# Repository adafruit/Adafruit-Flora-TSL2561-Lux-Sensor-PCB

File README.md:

## Adafruit Flora TSL2561 Lux Sensor PCB

<a href="http://www.adafruit.com/products/1246"><br/>
Click here to purchase one from the Adafruit shop</a>

PCB files for the Adafruit Flora TSL2561 Lux Sensor. Format is EagleCAD schematic and board layout
* https://www.adafruit.com/product/1246

### DESCRIPTION
Add light-reactive sensing to your wearable Flora project with this high precision Lux sensor. The TSL2561 luminosity sensor is an advanced digital light sensor, ideal for use in a wide range of light situations. Compared to low cost CdS cells, this sensor is more precise, allowing for exact lux calculations and can be configured for different gain/timing ranges to detect light ranges from up to 0.1 - 40,000+ Lux on the fly. The best part of this sensor is that it contains both infrared and full spectrum diodes! That means you can separately measure infrared, full-spectrum or human-visible light. Most sensors can only detect one or the other, which does not accurately represent what human eyes see (since we cannot perceive the IR light that is detected by most photo diodes)

The sensor has a digital (I2C) interface. Attaching it to the flora is simple: line up the sensor so its adjacent to the SDA/SCL pins and sew conductive thread from the 3V, SDA, SCL and GND pins. They line up perfectly so you will not have any crossed lines. You can only connect one lux sensor to your Flora, but you can connect other I2C sensors/outputs by using the set of SCL/SDA pins on the opposite side. The current draw is extremely low, about 0.5mA when actively sensing, and less than 15 uA when in powerdown mode.

### License

Adafruit invests time and resources providing this open source design, please support Adafruit and open-source hardware by purchasing products from [Adafruit.com](https://www.adafruit.com)!

Designed by Adafruit Industries. 

Creative Commons Attribution, Share-Alike license, check license.txt for more information All text above must be included in any redistribution - see license.txt for more information.

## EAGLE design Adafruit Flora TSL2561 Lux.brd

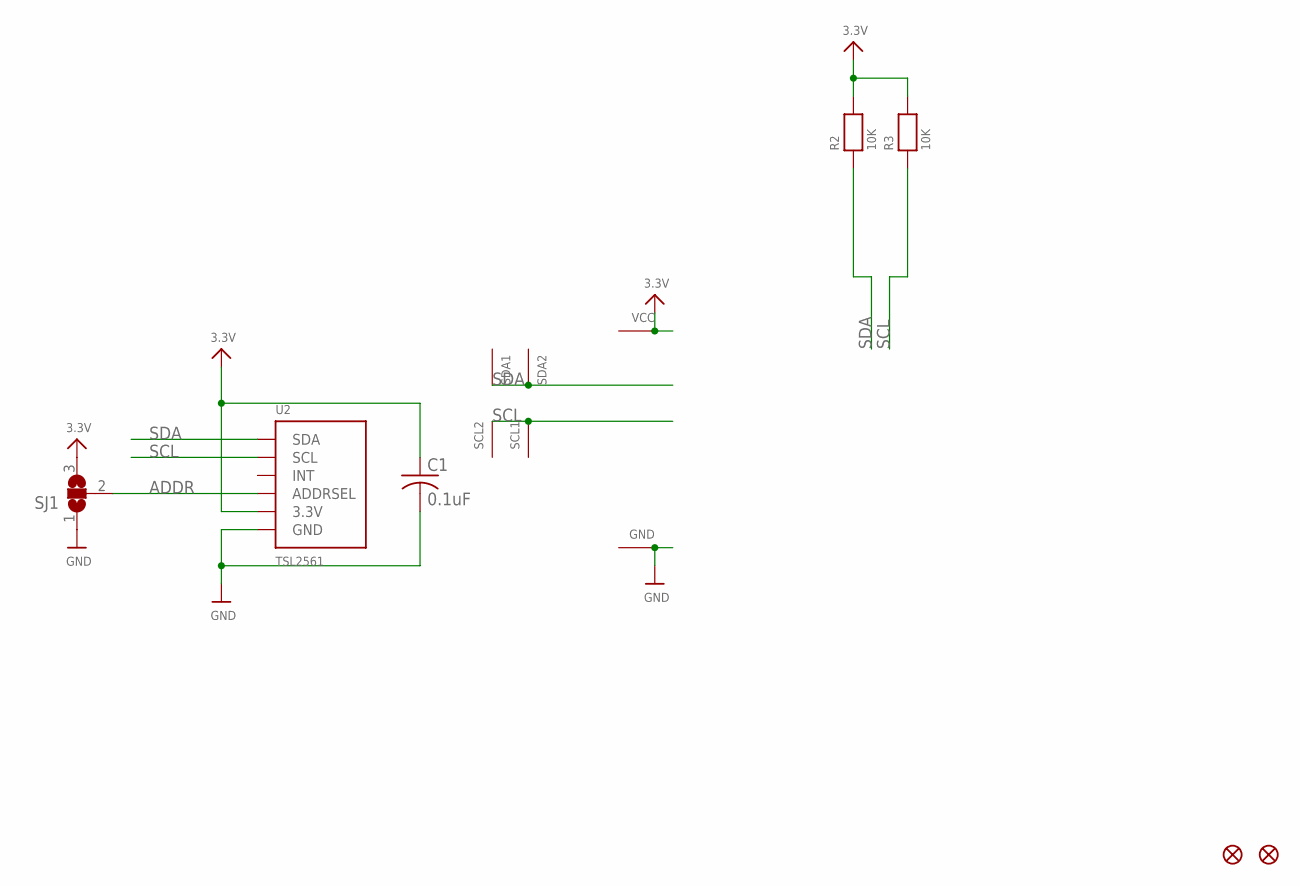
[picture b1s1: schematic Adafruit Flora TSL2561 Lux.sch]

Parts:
C1: 0.1uF; C0805K
FID1, FID2: FIDUCIAL""; FIDUCIAL_1MM
GND: SEWTAP0.5IN; SEWINGTAP_0.5
R2, R3: 10K; _0805
SCL1, SCL2: SEWTAP0.5IN; SEWINGTAP_0.5
SDA1, SDA2: SEWTAP0.5IN; SEWINGTAP_0.5
SJ1: SJ2W; SJ_2
U2: TSL2561; TSL2561_FN
VCC: SEWTAP0.5IN; SEWINGTAP_0.5

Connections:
3.3V: C1.1, R2.2, R3.2, SJ1.3, U2.VDD (3.3V), VCC.TAP
ADDR: SJ1.2, U2.ADR (ADDRSEL)
GND: C1.2, GND.TAP, SJ1.1, U2.VSS (GND)
SCL: R3.1, SCL1.TAP, SCL2.TAP, U2.CLK (SCL)
SDA: R2.1, SDA1.TAP, SDA2.TAP, U2.DATA (SDA)

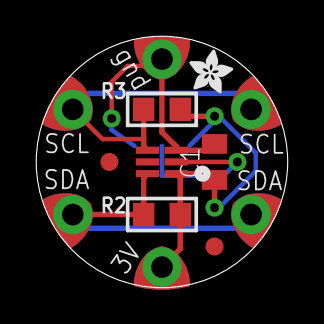
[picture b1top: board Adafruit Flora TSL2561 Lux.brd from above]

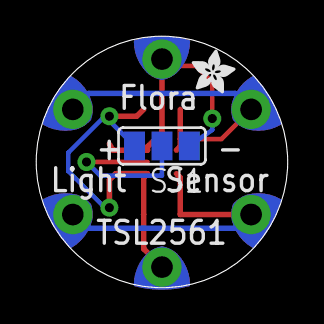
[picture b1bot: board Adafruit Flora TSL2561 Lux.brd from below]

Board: 2 copper layers, 14.0 x 14.0 mm, 15 parts (2 on the bottom side), 5 nets.

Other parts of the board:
U$3, U$4: ADAFRUIT_2.5MM

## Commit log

2016-09-30 init

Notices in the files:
parts and their libraries:
microbuilder: This work is placed in the public domain, and may be freely used for commercial and non-commercial work with the following conditions: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
